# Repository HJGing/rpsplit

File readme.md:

# rpsplit

*A short description of the keyboard/project*

* Keyboard Maintainer: [Heonjung Kim](https://github.com/HJGING)
* Hardware Supported: *The PCBs, controllers supported*
* Hardware Availability: *Links to where you can find this hardware*

Make example for this keyboard (after setting up your build environment):

    make rpsplit:default

Flashing example for this keyboard:

    make rpsplit:default:flash

See the [build environment setup](https://docs.qmk.fm/#/getting_started_build_tools) and the [make instructions](https://docs.qmk.fm/#/getting_started_make_guide) for more information. Brand new to QMK? Start with our [Complete Newbs Guide](https://docs.qmk.fm/#/newbs).

## Bootloader

Enter the bootloader in 3 ways:

* **Bootmagic reset**: Hold down the key at (0,0) in the matrix (usually the top left key or Escape) and plug in the keyboard
* **Physical reset button**: Briefly press the button on the back of the PCB - some may have pads you must short instead
* **Keycode in layout**: Press the key mapped to `QK_BOOT` if it is available

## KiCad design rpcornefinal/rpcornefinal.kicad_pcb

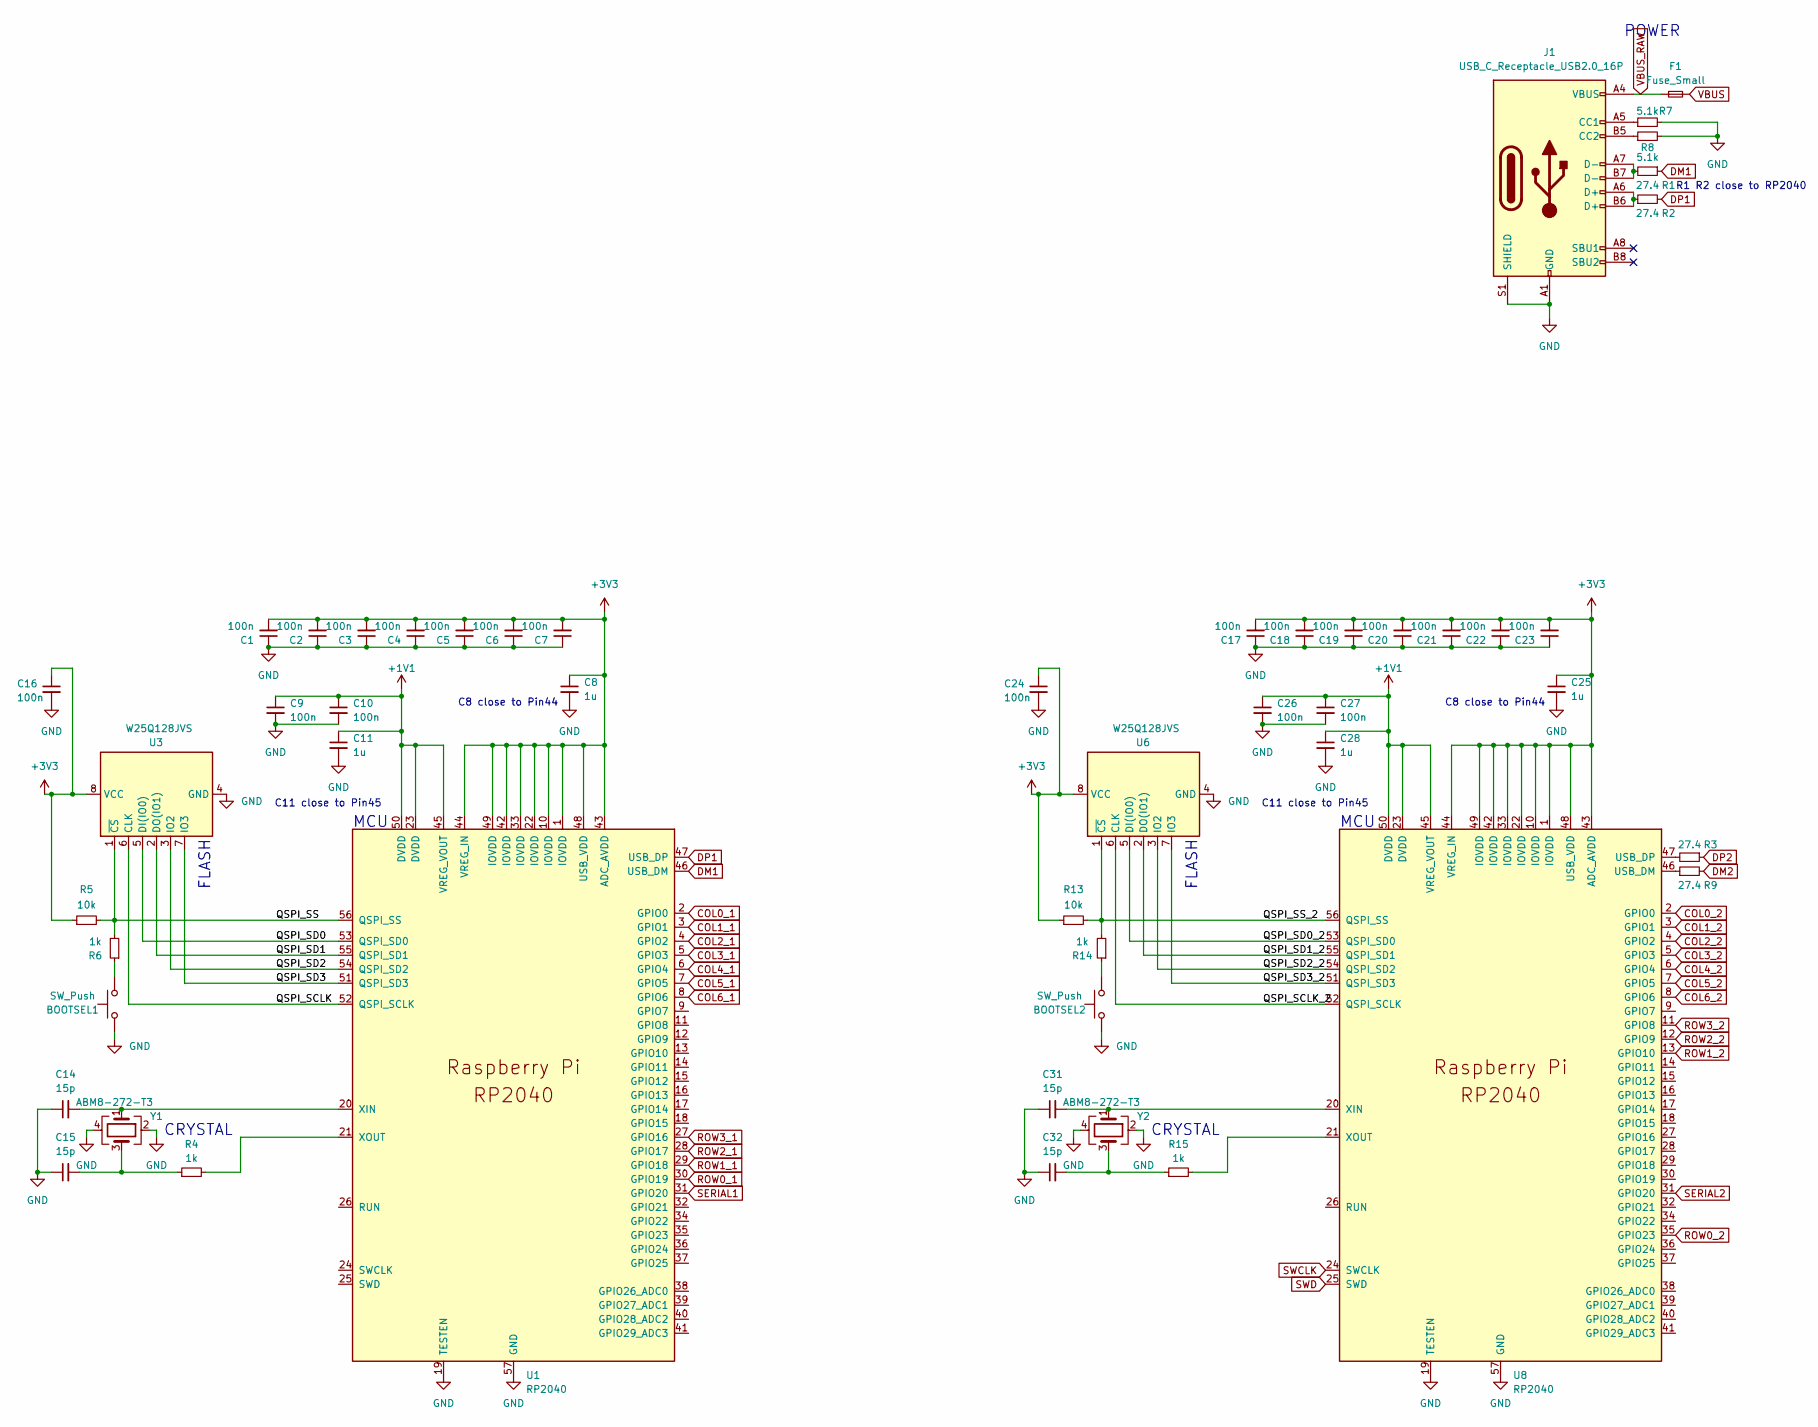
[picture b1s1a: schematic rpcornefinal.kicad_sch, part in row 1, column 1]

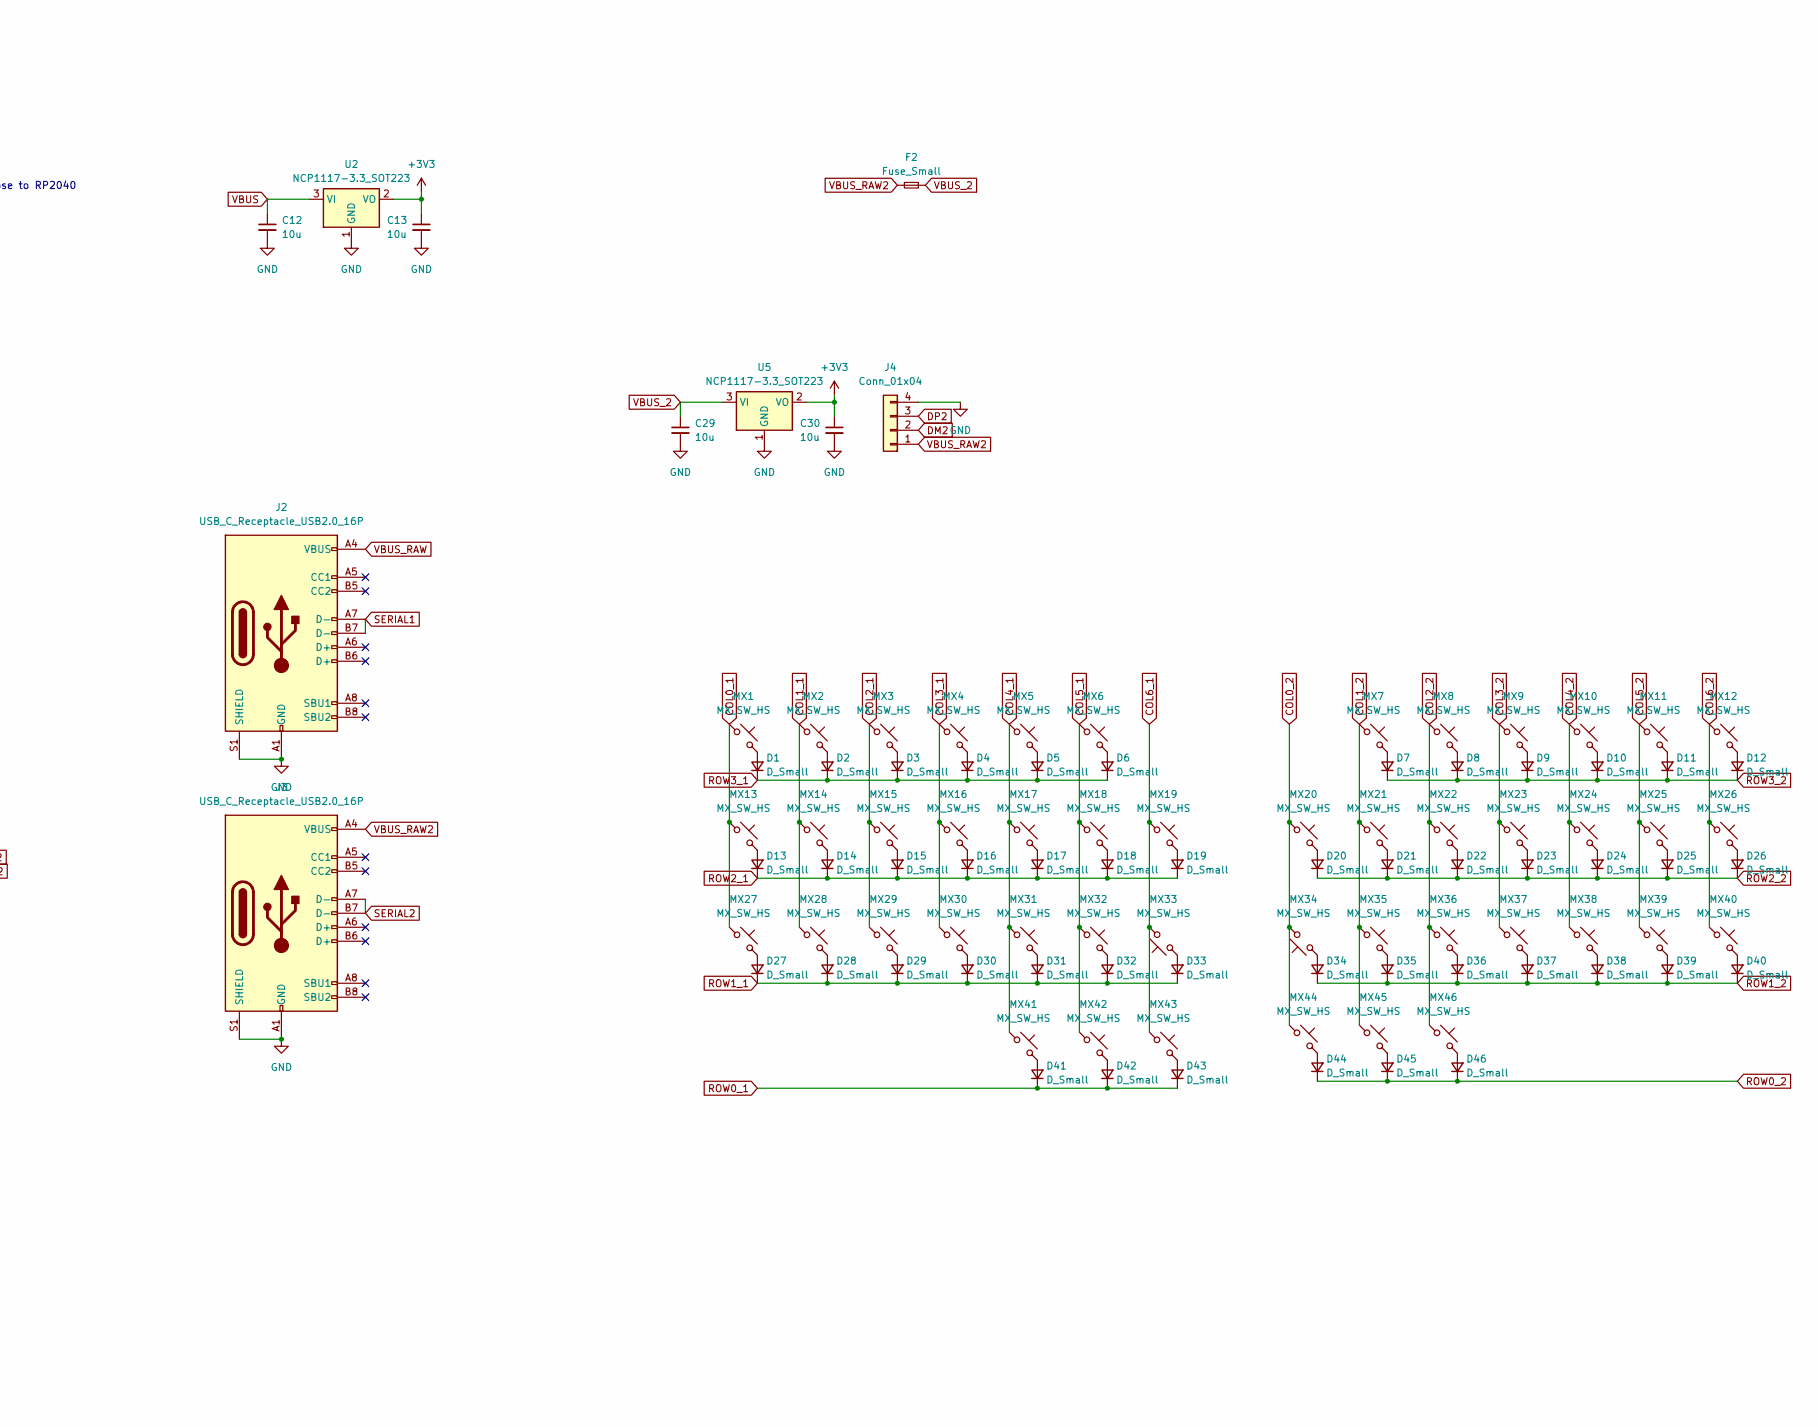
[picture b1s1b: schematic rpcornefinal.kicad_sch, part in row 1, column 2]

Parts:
BOOTSEL1, BOOTSEL2: SW_Push; SW_Push_1P1T_XKB_TS-1187A
C1, C2, C3, C4, C5, C6, C7, C9, C10, C16, C17, C18, C19, C20, C21, C22, C23, C24, C26, C27: 100n; C_0805_2012Metric
C8, C11, C25, C28: 1u; C_0805_2012Metric
C12, C13, C29, C30: 10u; C_0805_2012Metric
C14, C15, C31, C32: 15p; C_0805_2012Metric
D1, D2, D3, D4, D5, D6, D7, D8, D9, D10, D11, D12, D13, D14, D15, D16, D17, D18, D19, D20, D21, D22, D23, D24, D25, D26, D27, D28, D29, D30, D31, D32, D33, D34, D35, D36, D37, D38, D39, D40, D41, D42, D43, D44, D45, D46: D_Small; Diode_SOD-123_REF0N1
F1, F2: Fuse_Small; Fuse_0805_2012Metric_Pad1.15x1.40mm_HandSolder
J1, J2, J3: USB_C_Receptacle_USB2.0_16P; USB_C_Receptacle_GCT_USB4105-xx-A_16P_TopMnt_Horizontal
J4: Conn_01x04; JST_SH_SM04B-SRSS-TB_1x04-1MP_P1.00mm_Horizontal
MX1, MX2, MX3, MX4, MX5, MX6, MX7, MX8, MX9, MX10, MX11, MX12, MX13, MX14, MX15, MX16, MX17, MX18, MX19, MX20, MX21, MX22, MX23, MX24, MX25, MX26, MX27, MX28, MX29, MX30, MX31, MX32, MX33, MX34, MX35, MX36, MX37, MX38, MX39, MX40, MX41, MX42, MX43, MX44, MX45, MX46: MX_SW_HS; MX_PCB_1.00u_rounded
R1, R2, R3, R9: 27.4; R_0805_2012Metric
R4, R6, R14, R15: 1k; R_0805_2012Metric
R5, R13: 10k; R_0805_2012Metric
R7, R8: 5.1k; R_0805_2012Metric
U1, U8: RP2040; RP2040-QFN-56-NOPAD
U2, U5: NCP1117-3.3_SOT223; SOT-223-3_TabPin2
U3, U6: W25Q128JVS; SOIC-8_5.23x5.23mm_P1.27mm
Y1, Y2: ABM8-272-T3; Oscillator_SMD_EuroQuartz_XO32-4Pin_3.2x2.5mm_HandSoldering

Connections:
+1V1: C9.1, C10.1, C11.1, C26.1, C27.1, C28.1, U1.23 (DVDD), U1.45 (VREG_VOUT), U1.50 (DVDD), U8.23 (DVDD), U8.45 (VREG_VOUT), U8.50 (DVDD)
+3V3: C1.2, C2.2, C3.2, C4.2, C5.2, C6.2, C7.2, C8.1, C13.1, C16.1, C17.2, C18.2, C19.2, C20.2, C21.2, C22.2, C23.2, C24.1, C25.1, C30.1, R5.1, R13.1, U1.1 (IOVDD), U1.10 (IOVDD), U1.22 (IOVDD), U1.33 (IOVDD), U1.42 (IOVDD), U1.43 (ADC_AVDD), U1.44 (VREG_IN), U1.48 (USB_VDD), U1.49 (IOVDD), U2.2 (VO), U3.8 (VCC), U5.2 (VO), U6.8 (VCC), U8.1 (IOVDD), U8.10 (IOVDD), U8.22 (IOVDD), U8.33 (IOVDD), U8.42 (IOVDD), U8.43 (ADC_AVDD), U8.44 (VREG_IN), U8.48 (USB_VDD), U8.49 (IOVDD)
/QSPI_SCLK: U1.52 (QSPI_SCLK), U3.6 (CLK)
/QSPI_SCLK_2: U6.6 (CLK), U8.52 (QSPI_SCLK)
/QSPI_SD0: U1.53 (QSPI_SD0), U3.5 (DI(IO0))
/QSPI_SD0_2: U6.5 (DI(IO0)), U8.53 (QSPI_SD0)
/QSPI_SD1: U1.55 (QSPI_SD1), U3.2 (DO(IO1))
/QSPI_SD1_2: U6.2 (DO(IO1)), U8.55 (QSPI_SD1)
/QSPI_SD2: U1.54 (QSPI_SD2), U3.3 (IO2)
/QSPI_SD2_2: U6.3 (IO2), U8.54 (QSPI_SD2)
/QSPI_SD3: U1.51 (QSPI_SD3), U3.7 (IO3)
/QSPI_SD3_2: U6.7 (IO3), U8.51 (QSPI_SD3)
/QSPI_SS: R5.2, R6.2, U1.56 (QSPI_SS), U3.1 (~CS)
/QSPI_SS_2: R13.2, R14.2, U6.1 (~CS), U8.56 (QSPI_SS)
COL0_1: MX1.1, MX13.1, MX27.1, U1.2 (GPIO0)
COL0_2: MX20.1, MX34.2, MX44.1, U8.2 (GPIO0)
COL1_1: MX2.1, MX14.1, MX28.1, U1.3 (GPIO1)
COL1_2: MX7.1, MX21.1, MX35.1, MX45.1, U8.3 (GPIO1)
COL2_1: MX3.1, MX15.1, MX29.1, U1.4 (GPIO2)
COL2_2: MX8.1, MX22.1, MX36.1, MX46.1, U8.4 (GPIO2)
COL3_1: MX4.1, MX16.1, MX30.1, U1.5 (GPIO3)
COL3_2: MX9.1, MX23.1, MX37.1, U8.5 (GPIO3)
COL4_1: MX5.1, MX17.1, MX31.1, MX41.1, U1.6 (GPIO4)
COL4_2: MX10.1, MX24.1, MX38.1, U8.6 (GPIO4)
COL5_1: MX6.1, MX18.1, MX32.1, MX42.1, U1.7 (GPIO5)
COL5_2: MX11.1, MX25.1, MX39.1, U8.7 (GPIO5)
COL6_1: MX19.1, MX33.2, MX43.1, U1.8 (GPIO6)
COL6_2: MX12.1, MX26.1, MX40.1, U8.8 (GPIO6)
DM1: R1.1, U1.46 (USB_DM)
DM2: J4.2, R9.2
DP1: R2.2, U1.47 (USB_DP)
DP2: J4.3, R3.1
GND: BOOTSEL1.1, BOOTSEL2.1, C1.1, C2.1, C3.1, C4.1, C5.1, C6.1, C7.1, C8.2, C9.2, C10.2, C11.2, C12.2, C13.2, C14.1, C15.1, C16.2, C17.1, C18.1, C19.1, C20.1, C21.1, C22.1, C23.1, C24.2, C25.2, C26.2, C27.2, C28.2, C29.2, C30.2, C31.1, C32.1, J1.A1 (GND), J1.A12 (GND), J1.B1 (GND), J1.B12 (GND), J1.S1 (SHIELD), J2.A1 (GND), J2.A12 (GND), J2.B1 (GND), J2.B12 (GND), J2.S1 (SHIELD), J3.A1 (GND), J3.A12 (GND), J3.B1 (GND), J3.B12 (GND), J3.S1 (SHIELD), J4.4, R7.2, R8.2, U1.19 (TESTEN), U1.57 (GND), U2.1 (GND), U3.4 (GND), U5.1 (GND), U6.4 (GND), U8.19 (TESTEN), U8.57 (GND), Y1.2, Y1.4, Y2.2, Y2.4
unnamed: BOOTSEL1.2, R6.1
unnamed: BOOTSEL2.2, R14.1
unnamed: C15.2, R4.1, Y1.3
unnamed: C32.2, R15.1, Y2.3
unnamed: D1.2 (A), MX1.2
unnamed: D2.2 (A), MX2.2
unnamed: D3.2 (A), MX3.2
unnamed: D4.2 (A), MX4.2
unnamed: D5.2 (A), MX5.2
unnamed: D6.2 (A), MX6.2
unnamed: D7.2 (A), MX7.2
unnamed: D8.2 (A), MX8.2
unnamed: D9.2 (A), MX9.2
unnamed: D10.2 (A), MX10.2
unnamed: D11.2 (A), MX11.2
unnamed: D12.2 (A), MX12.2
unnamed: D13.2 (A), MX13.2
unnamed: D14.2 (A), MX14.2
unnamed: D15.2 (A), MX15.2
unnamed: D16.2 (A), MX16.2
unnamed: D17.2 (A), MX17.2
unnamed: D18.2 (A), MX18.2
unnamed: D19.2 (A), MX19.2
unnamed: D20.2 (A), MX20.2
unnamed: D21.2 (A), MX21.2
unnamed: D22.2 (A), MX22.2
unnamed: D23.2 (A), MX23.2
unnamed: D24.2 (A), MX24.2
unnamed: D25.2 (A), MX25.2
unnamed: D26.2 (A), MX26.2
unnamed: D27.2 (A), MX27.2
unnamed: D28.2 (A), MX28.2
unnamed: D29.2 (A), MX29.2
unnamed: D30.2 (A), MX30.2
unnamed: D31.2 (A), MX31.2
unnamed: D32.2 (A), MX32.2
unnamed: D33.2 (A), MX33.1
unnamed: D34.2 (A), MX34.1
unnamed: D35.2 (A), MX35.2
unnamed: D36.2 (A), MX36.2
unnamed: D37.2 (A), MX37.2
unnamed: D38.2 (A), MX38.2
unnamed: D39.2 (A), MX39.2
unnamed: D40.2 (A), MX40.2
unnamed: D41.2 (A), MX41.2
unnamed: D42.2 (A), MX42.2
unnamed: D43.2 (A), MX43.2
unnamed: D44.2 (A), MX44.2
unnamed: D45.2 (A), MX45.2
unnamed: D46.2 (A), MX46.2
unnamed: J1.A5 (CC1), R7.1
unnamed: J1.B5 (CC2), R8.1
unnamed: J1.A6 (D+), J1.B6 (D+), R2.1
unnamed: J1.A7 (D-), J1.B7 (D-), R1.2
unnamed: C14.2, U1.20 (XIN), Y1.1
unnamed: R4.2, U1.21 (XOUT)
unnamed: R9.1, U8.46 (USB_DM)
unnamed: R3.2, U8.47 (USB_DP)
unnamed: C31.2, U8.20 (XIN), Y2.1
unnamed: R15.2, U8.21 (XOUT)
ROW0_1: D41.1 (K), D42.1 (K), D43.1 (K), U1.30 (GPIO19)
ROW0_2: D44.1 (K), D45.1 (K), D46.1 (K), U8.35 (GPIO23)
ROW1_1: D27.1 (K), D28.1 (K), D29.1 (K), D30.1 (K), D31.1 (K), D32.1 (K), D33.1 (K), U1.29 (GPIO18)
ROW1_2: D34.1 (K), D35.1 (K), D36.1 (K), D37.1 (K), D38.1 (K), D39.1 (K), D40.1 (K), U8.13 (GPIO10)
ROW2_1: D13.1 (K), D14.1 (K), D15.1 (K), D16.1 (K), D17.1 (K), D18.1 (K), D19.1 (K), U1.28 (GPIO17)
ROW2_2: D20.1 (K), D21.1 (K), D22.1 (K), D23.1 (K), D24.1 (K), D25.1 (K), D26.1 (K), U8.12 (GPIO9)
ROW3_1: D1.1 (K), D2.1 (K), D3.1 (K), D4.1 (K), D5.1 (K), D6.1 (K), U1.27 (GPIO16)
ROW3_2: D7.1 (K), D8.1 (K), D9.1 (K), D10.1 (K), D11.1 (K), D12.1 (K), U8.11 (GPIO8)
SERIAL1: J2.A7 (D-), J2.B7 (D-), U1.31 (GPIO20)
SERIAL2: J3.A7 (D-), J3.B7 (D-), U8.31 (GPIO20)
SWCLK: U8.24 (SWCLK)
SWD: U8.25 (SWD)
VBUS: C12.1, F1.2, U2.3 (VI)
VBUS_2: C29.1, F2.2, U5.3 (VI)
VBUS_RAW: F1.1, J1.A4 (VBUS), J1.A9 (VBUS), J1.B4 (VBUS), J1.B9 (VBUS), J2.A4 (VBUS), J2.A9 (VBUS), J2.B4 (VBUS), J2.B9 (VBUS)
VBUS_RAW2: F2.1, J3.A4 (VBUS), J3.A9 (VBUS), J3.B4 (VBUS), J3.B9 (VBUS), J4.1

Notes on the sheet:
C11 close to Pin45
MCU
CRYSTAL
POWER
FLASH
C8 close to Pin44
R1 R2 close to RP2040

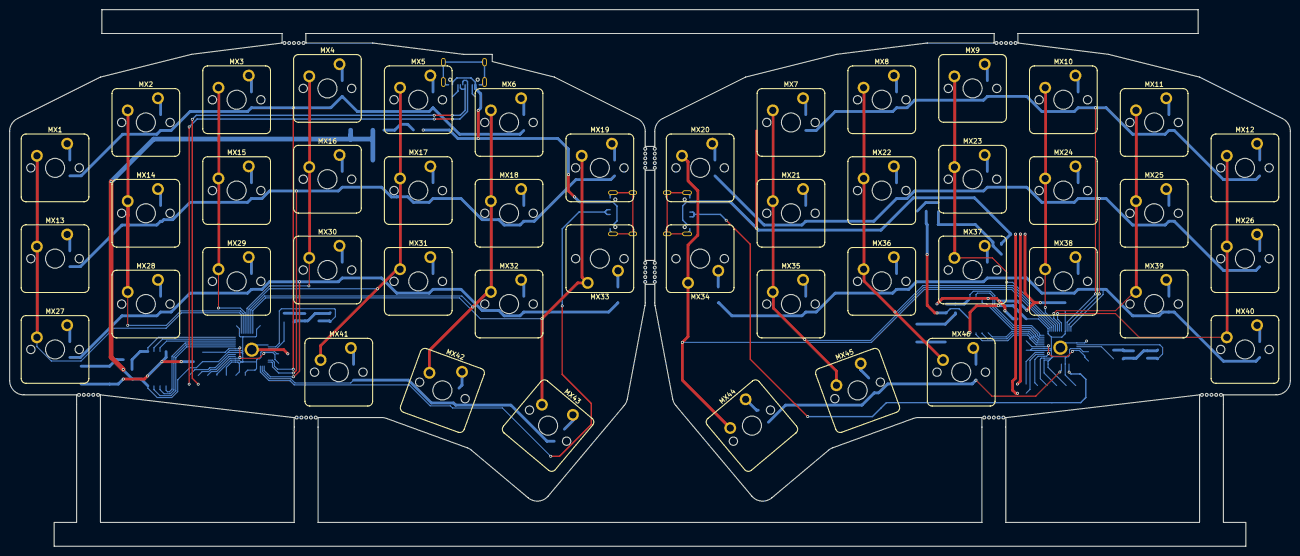
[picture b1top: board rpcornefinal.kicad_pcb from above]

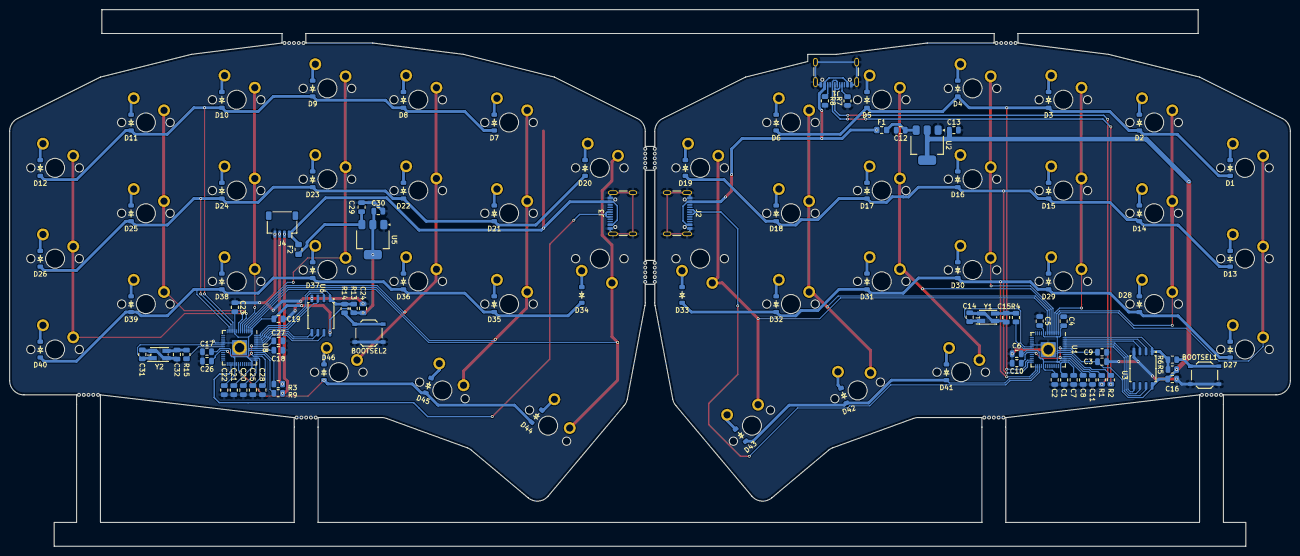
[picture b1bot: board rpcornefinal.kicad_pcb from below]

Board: 2 copper layers, 268.7 x 112.6 mm, 152 parts (106 on the bottom side), 107 nets.
